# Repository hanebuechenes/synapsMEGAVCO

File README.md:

# synapsVCO 🎛️⚡

**synapsVCO** ist ein kompakter, leistungsstarker und professioneller Eurorack-Wavetable-VCO (Voltage Controlled Oscillator) auf Basis des **ATmega328P** Mikrocontrollers. Entwickelt für performative Live-Einsätze, kombiniert das Modul eine rauscharme analoge Signalverarbeitung mit mächtigen digitalen Klangformungsmöglichkeiten auf ultra-kompakten **6 TE** (30,48 mm).

## 🔬 Hauptmerkmale & Features

* **High-Performance Audio Path:**
  * Dual 12-Bit DAC (**MCP4922**) für hochauflösende Audiosignale.
  * Symmetrische Pufferung und Rekonstruktionsfilterung über Quad Op-Amp (**TL074**).

* **Killer Performance-Features:**
  * **Hard-Sync (`SYNC_IN`):** Triggert sofortigen Phasen-Reset an Interrupt-Pin `PD0` für aggressive Lead-Sounds und Sync-Sweeps.
  * **Morph-CV (`MORPH_CV`):** Gepufferter CV-Modulationseingang (über TL074 auf ADC `PC3`) zur dynamischen Modulation von Wavetables, Wave-Folding oder Pulsweite.
  * **Hardware Sub-Oszillator (`SUB_OUT`):** Dezidierter Auskopplungspfad (1 Oktave tiefer) über ATmega-Digitalpin `PD6` mit DC-Blocker für solides Bass-Fundament.

* **Audio- & Kontroll-Schnittstellen:**
  * **1V/Oct Pitch CV (`CV_IN`):** Impedanzgewandelter Eingangs-Pfad mit Zener-Diodenschutz.
  * **Gate In (`GATE_IN`) & Clock In (`CLOCK_IN`):** Dedizierte Digital-Eingänge für rhythmische Noten- und Takt-Trigger.
  * **Stereo/Dual Audio-Out (`AudioOut_L` / `AudioOut_R`).**

* **Robuste Stromversorgung & Protection:**
  * Bipolare $\pm 12\text{V}$ Eurorack-Versorgung.
  * Schutz vor Verpolung durch Schottky-Dioden (`MBRA140T3G`) und rückstellende Polyfuses (`250mA`).
  * Rauschfreie $\pm 12\text{VA}$ Analogschienen durch LC-Filterung (Ferrite Beads `120R@100MHz` + Entkopplungskondensatoren).
  * Effizienter Onboard 5V DC/DC-Schaltregler (`TPS54302`).

## 📏 Formfaktor & Layout

* **Breite:** 6 TE (30,48 mm)
* **Höhe:** Standard Eurorack 3U (128,5 mm Frontplatte / ~108,5 mm Platine)
* **Bauteil-Spezifikation:** Durchgängig **0603 SMD-Komponenten** (resistors/caps) für optimale Packungsdichte bei hervorragender manueller Lötbarkeit.

## 🛠️ Hardware-Architektur & Belegung

### Pin-Mapping (ATmega328P-AU TQFP-32)

| Pin | Symbol / Net | Funktion / Beschreibung |
| :--- | :--- | :--- |
| **Pin 30** | `PD0` | **Hard-Sync Input** (External Interrupt) |
| **Pin 32** | `PD2` | **Gate Input** |
| **Pin 1** | `PD3` | **Clock Input** |
| **Pin 10** | `PD6` | **Sub-Oszillator Output** |
| **Pin 25** | `PC2 / ADC2` | **1V/Oct CV Input** |
| **Pin 26** | `PC3 / ADC3` | **Morph-CV Input** |
| **Pin 23 / 24** | `PC0 / PC1` | **Potentiometer 1 & 2** (Parametertrimmer) |
| **Pin 14–17** | `PB2–PB5` | **SPI Interface** (MCP4922 DAC Steuerung) |
| **Pin 7 / 8** | `XTAL1 / XTAL2` | **16 MHz Quarz-Taktgeber** |

## 📋 Bauteilübersicht (BOM Kurzfassung)

* **Microcontroller:** ATmega328P-AU (TQFP-32)
* **DAC:** MCP4922-E/SL (SOIC-14)
* **Op-Amp:** TL074CDR (SOIC-14)
* **Power Regulator:** TPS54302 (SOT-23-6)
* **Dioden:** MBRA140T3G (SMA), B340A (SMA), 5.1V Zener (SOD-123)
* **Buchsen:** 3.5mm PJ301M-12 (THT)
* **Potentiometer:** Alpha RK09K Serie (THT)

## ⚡ Inbetriebnahme & Flashen

1. **Power-Check:** Vor dem Einsetzen von ICs oder der Firmware-Programmierung sicherstellen, dass an den Power-Rails des TL074 $+12\text{V}$ (Pin 4) und $-12\text{V}$ (Pin 11) anliegen sowie die Mikrocontroller-Schiene exakt $+5\text{V}$ aufweist.
2. **ISP-Programming:** Das Modul verfügt über einen Standard **2x3-Pin ISP Header** (`J2`).
3. **Fuses setzen:** Für den externen 16 MHz Quarz (`Y2`):
   * High Fuse: `0xD9`
   * Low Fuse: `0xFF`
   * Extended Fuse: `0xFD`

## 📄 Lizenz

Dieses Projekt ist Open-Source-Hardware unter der **CERN-OHL-P (Permissive)** Lizenz.

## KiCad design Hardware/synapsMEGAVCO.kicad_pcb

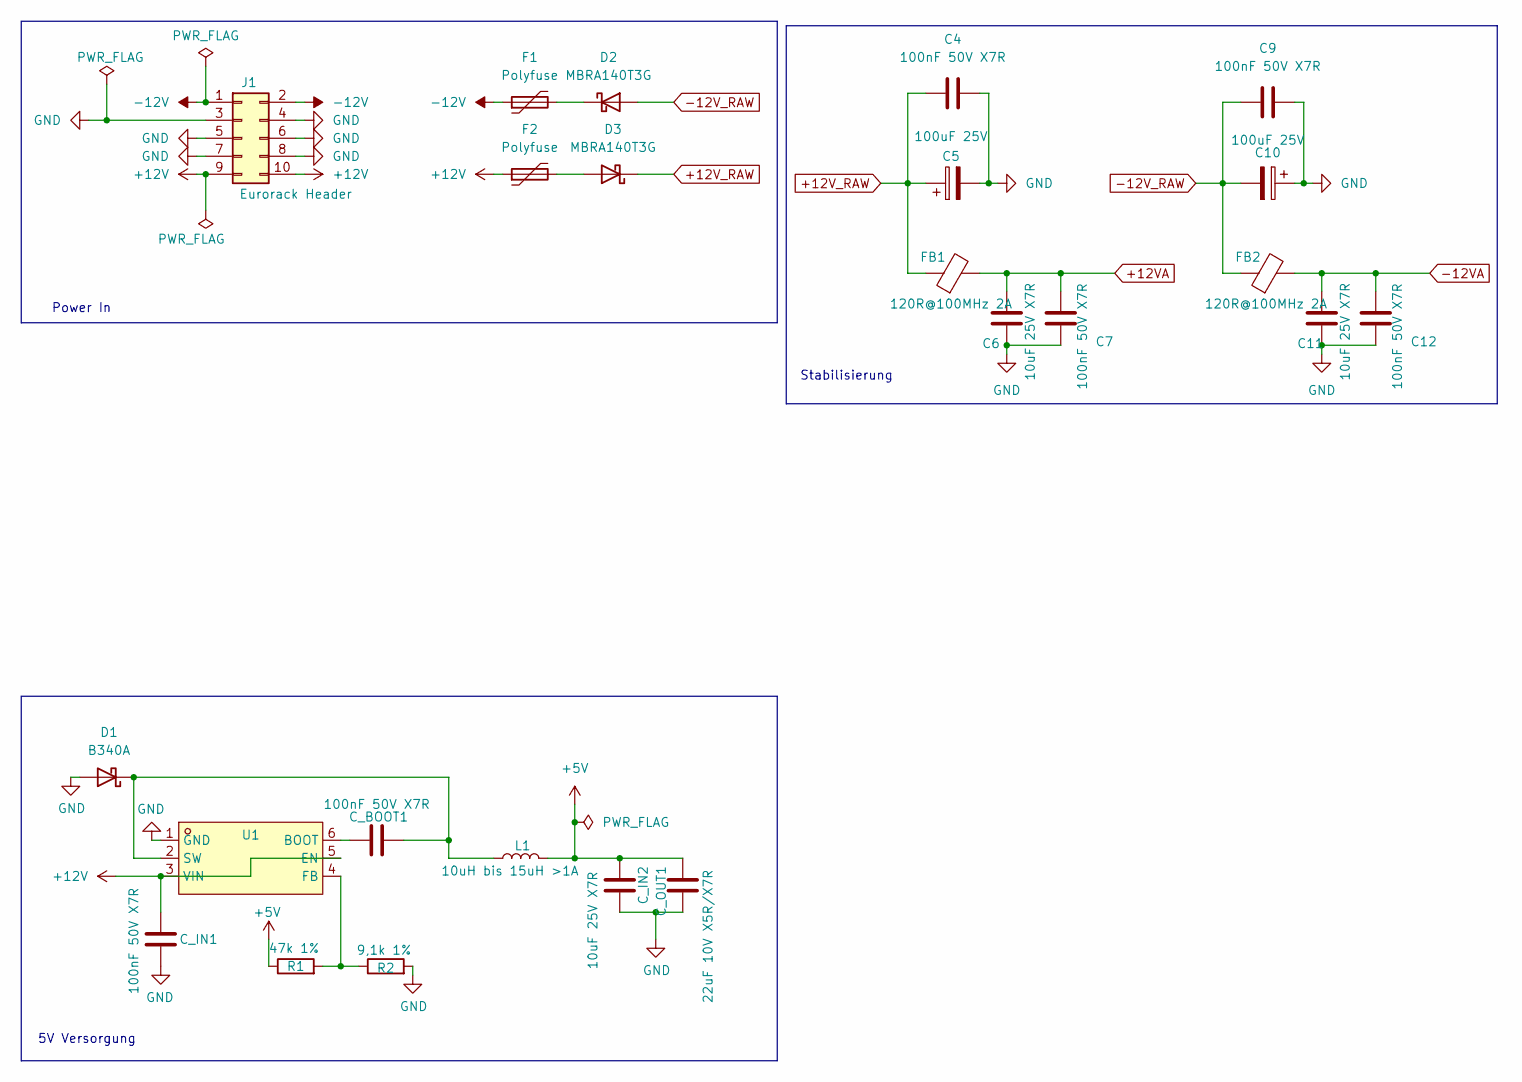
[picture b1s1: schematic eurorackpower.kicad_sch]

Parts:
C4, C7, C9, C12: 100nF 50V X7R; C_0603_1608Metric_Pad1.08x0.95mm_HandSolder
C5, C10: 100uF 25V; CP_Elec_6.3x7.7
C6, C11: 10uF 25V X7R; C_0805_2012Metric_Pad1.18x1.45mm_HandSolder
C_BOOT1: 100nF 50V X7R; C_0603_1608Metric_Pad1.08x0.95mm_HandSolder
C_IN1: 100nF 50V X7R; C_0603_1608Metric_Pad1.08x0.95mm_HandSolder
C_IN2: 10uF 25V X7R; C_0805_2012Metric_Pad1.18x1.45mm_HandSolder
C_OUT1: 22uF 10V X5R/X7R; C_0805_2012Metric_Pad1.18x1.45mm_HandSolder
D1: B340A; D_SMA
D2, D3: MBRA140T3G; D_SMA
F1, F2: Polyfuse; Fuse_1210_3225Metric
FB1, FB2: 120R@100MHz 2A; L_0603_1608Metric_Pad1.05x0.95mm_HandSolder
J1: Eurorack Header; PinHeader_2x05_P2.54mm_Vertical
L1: 10uH bis 15uH >1A; L_Coilcraft_XxL4030
R1: 47k 1%; R_0603_1608Metric_Pad0.98x0.95mm_HandSolder
R2: 9,1k 1%; R_0603_1608Metric_Pad0.98x0.95mm_HandSolder
U1: TPS54302DDCR_C311983; SOT-23-6_L2.9-W1.6-P0.95-LS2.8-BL; MPN TPS54302DDCR; LCSC Part C311983

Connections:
+5V: C_IN2.1, C_OUT1.1, L1.2, R1.1; also elsewhere on the board
+12V: C_IN1.1, F2.1, J1.9, J1.10, U1.3 (VIN), U1.5 (EN)
+12VA: C6.1, C7.1, FB1.2; also elsewhere on the board
+12V_RAW: C4.1, C5.1, D3.1 (K), FB1.1
-12V: F1.1, J1.1, J1.2
-12VA: C11.1, C12.1, FB2.2; also elsewhere on the board
-12V_RAW: C9.1, C10.2, D2.2 (A), FB2.1
GND: C4.2, C5.2, C6.2, C7.2, C9.2, C10.1, C11.2, C12.2, C_IN1.2, C_IN2.2, C_OUT1.2, D1.2 (A), J1.3, J1.4, J1.5, J1.6, J1.7, J1.8, R2.2, U1.1 (GND); also elsewhere on the board
unnamed: C_BOOT1.2, D1.1 (K), L1.1, U1.2 (SW)
unnamed: D2.1 (K), F1.2
unnamed: D3.2 (A), F2.2
unnamed: C_BOOT1.1, U1.6 (BOOT)
unnamed: R1.2, R2.1, U1.4 (FB)

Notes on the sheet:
5V Versorgung
Power In
Stabilisierung

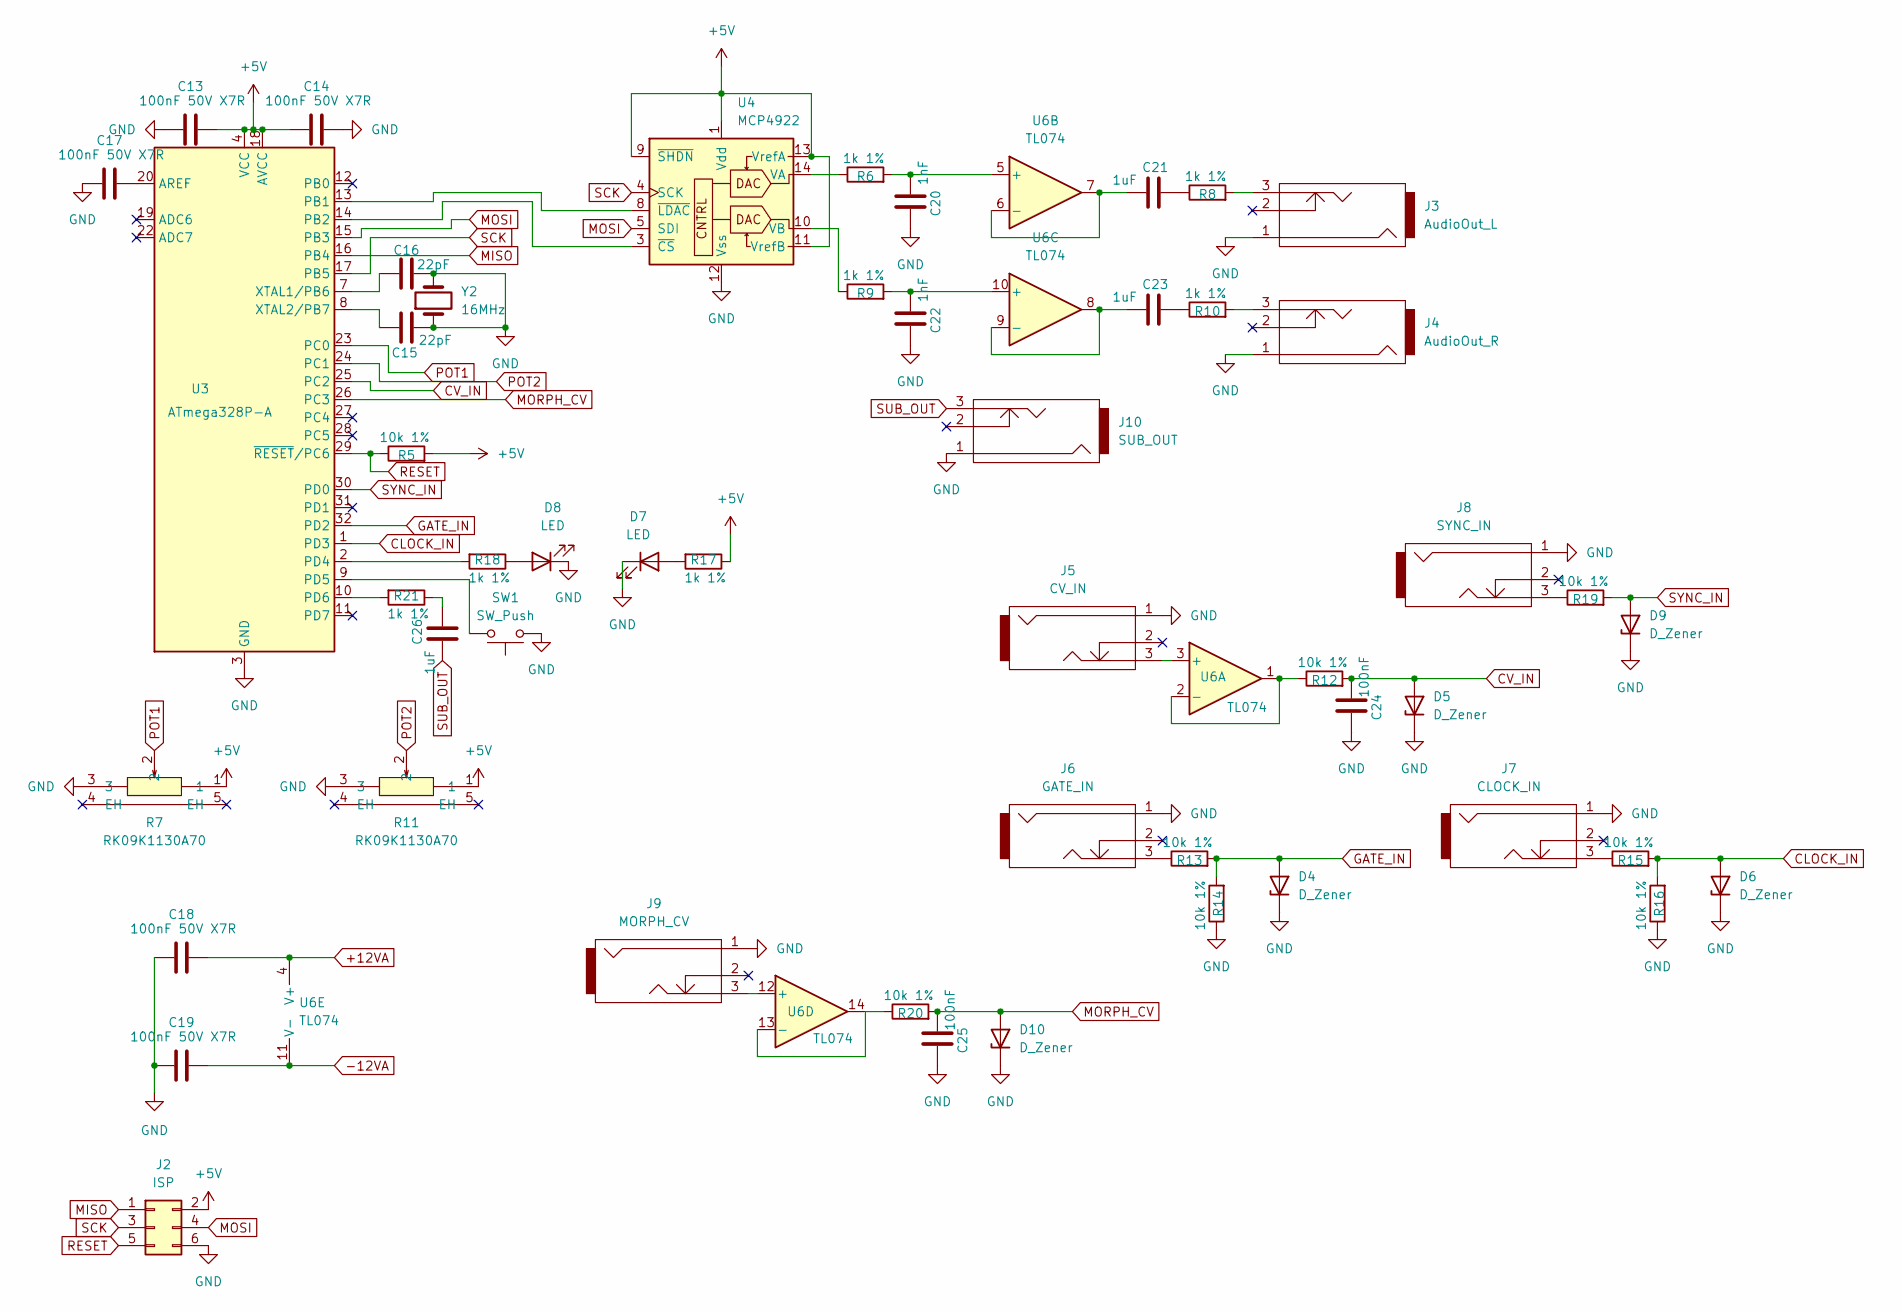
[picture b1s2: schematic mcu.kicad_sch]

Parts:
C13, C14, C17, C18, C19: 100nF 50V X7R; C_0603_1608Metric_Pad1.08x0.95mm_HandSolder
C15, C16: 22pF; C_0603_1608Metric_Pad1.08x0.95mm_HandSolder
C20, C22: 1nF; C_0603_1608Metric_Pad1.08x0.95mm_HandSolder
C21, C23, C26: 1uF; C_0603_1608Metric_Pad1.08x0.95mm_HandSolder
C24, C25: 100nF; C_0603_1608Metric_Pad1.08x0.95mm_HandSolder
D4, D5, D6, D9, D10: D_Zener; D_SOD-123
D7, D8: LED; led-3mm
J2: ISP; PinHeader_2x03_P2.54mm_Vertical
J3: AudioOut_L; PJ301M-12; MFG Part Number WQP-WQP518MA; Digikey Part Number N/A
J4: AudioOut_R; PJ301M-12; MFG Part Number WQP-WQP518MA; Digikey Part Number N/A
J5: CV_IN; PJ301M-12; MFG Part Number WQP-WQP518MA; Digikey Part Number N/A
J6: GATE_IN; PJ301M-12; MFG Part Number WQP-WQP518MA; Digikey Part Number N/A
J7: CLOCK_IN; PJ301M-12; MFG Part Number WQP-WQP518MA; Digikey Part Number N/A
J8: SYNC_IN; PJ301M-12; MFG Part Number WQP-WQP518MA; Digikey Part Number N/A
J9: MORPH_CV; PJ301M-12; MFG Part Number WQP-WQP518MA; Digikey Part Number N/A
J10: SUB_OUT; PJ301M-12; MFG Part Number WQP-WQP518MA; Digikey Part Number N/A
R5, R12, R13, R14, R15, R16, R19, R20: 10k 1%; R_0603_1608Metric_Pad0.98x0.95mm_HandSolder
R6, R8, R9, R10, R17, R18, R21: 1k 1%; R_0603_1608Metric_Pad0.98x0.95mm_HandSolder
R7, R11: RK09K1130A70; RES-TH_RK09K1130A70; MPN RK09K1130A70; LCSC Part C351173
SW1: SW_Push; SW_PUSH_6mm
U3: ATmega328P-A; TQFP-32_7x7mm_P0.8mm
U4: MCP4922; SOIC-14_3.9x8.7mm_P1.27mm
U6: TL074; SOIC-14_L8.7-W3.9-P1.27-LS6.0-BL
Y2: 16MHz; Crystal_HC49-U_Vertical

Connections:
+5V: C13.2, C14.1, J2.2, R5.2, R7.1, R11.1, R17.1, U3.4 (VCC), U3.6 (VCC), U3.18 (AVCC), U4.1 (Vdd), U4.9 (~SHDN), U4.11 (VrefB), U4.13 (VrefA); also elsewhere on the board
+12VA: C18.2, U6.4 (V+); also elsewhere on the board
-12VA: C19.2, U6.11 (V-); also elsewhere on the board
CLOCK_IN: D6.2 (A), R15.2, R16.2, U3.1 (PD3)
CV_IN: C24.2, D5.2 (A), R12.2, U3.25 (PC2)
GATE_IN: D4.2 (A), R13.2, R14.2, U3.32 (PD2)
GND: C13.1, C14.2, C15.2, C16.2, C17.1, C18.1, C19.1, C20.1, C22.1, C24.1, C25.1, D4.1 (K), D5.1 (K), D6.1 (K), D7.1 (K), D8.1 (K), D9.1 (K), D10.1 (K), J2.6, J3.1, J4.1, J5.1, J6.1, J7.1, J8.1, J9.1, J10.1, R7.3, R11.3, R14.1, R16.1, SW1.1, U3.3 (GND), U3.5 (GND), U3.21 (GND), U4.12 (Vss), Y2.1, Y2.2; also elsewhere on the board
MISO: J2.1, U3.16 (PB4)
MORPH_CV: C25.2, D10.2 (A), R20.2, U3.26 (PC3)
MOSI: J2.4, U3.15 (PB3), U4.5 (SDI)
unnamed: C21.1, R8.1
unnamed: C23.1, R10.1
unnamed: C26.1, R21.1
unnamed: D7.2 (A), R17.2
unnamed: D8.2 (A), R18.1
unnamed: J3.3, R8.2
unnamed: J4.3, R10.2
unnamed: J6.3, R13.1
unnamed: J7.3, R15.1
unnamed: J8.3, R19.1
unnamed: C17.2, U3.20 (AREF)
unnamed: U3.13 (PB1), U4.8 (~LDAC)
unnamed: U3.14 (PB2), U4.3 (~CS)
unnamed: R18.2, U3.2 (PD4)
unnamed: SW1.2, U3.9 (PD5)
unnamed: R21.2, U3.10 (PD6)
unnamed: C16.1, U3.7 (XTAL1/PB6)
unnamed: C15.1, U3.8 (XTAL2/PB7)
unnamed: R6.1, U4.14 (VA)
unnamed: R9.1, U4.10 (VB)
unnamed: J5.3, U6.3 (+)
unnamed: R12.1, U6.1, U6.2 (-)
unnamed: C20.2, R6.2, U6.5 (+)
unnamed: C21.2, U6.6 (-), U6.7
unnamed: C22.2, R9.2, U6.10 (+)
unnamed: C23.2, U6.8, U6.9 (-)
unnamed: J9.3, U6.12 (+)
unnamed: R20.1, U6.13 (-), U6.14
POT1: R7.2, U3.23 (PC0)
POT2: R11.2, U3.24 (PC1)
RESET: J2.5, R5.1, U3.29 (~RESET/PC6)
SCK: J2.3, U3.17 (PB5), U4.4 (SCK)
SUB_OUT: C26.2, J10.3
SYNC_IN: D9.2 (A), R19.2, U3.30 (PD0)

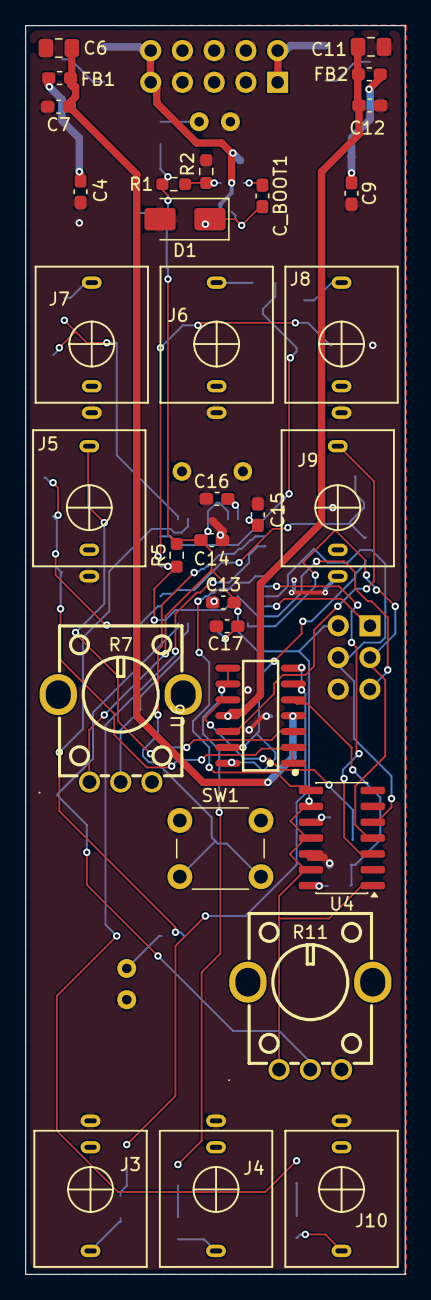
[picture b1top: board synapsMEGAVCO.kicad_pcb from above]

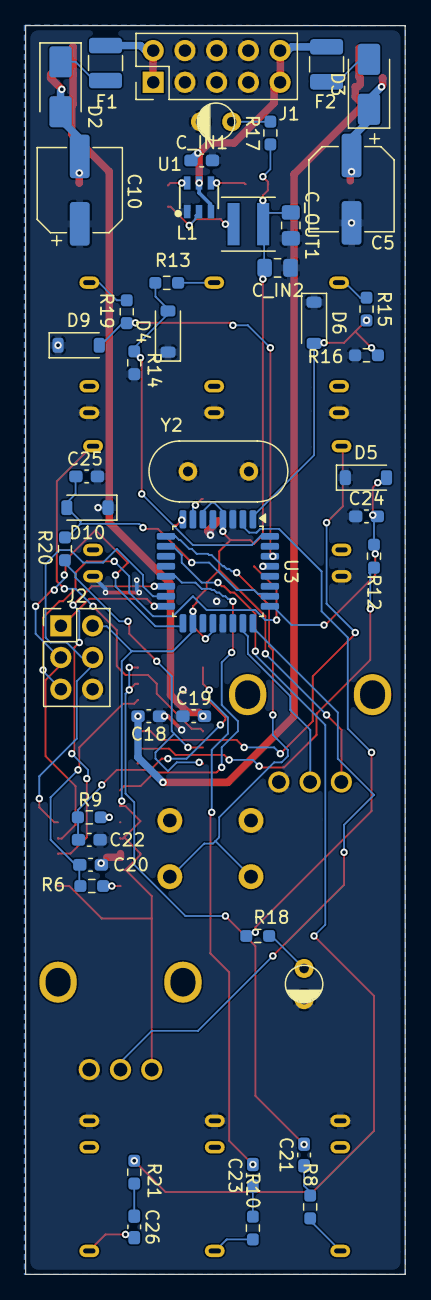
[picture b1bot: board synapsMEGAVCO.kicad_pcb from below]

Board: 2 copper layers, 30.4 x 100.0 mm, 76 parts (45 on the bottom side), 53 nets.

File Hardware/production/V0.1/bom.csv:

Designator,Footprint,Quantity,Value,LCSC Part #
"C10, C5",CP_Elec_6.3x7.7,2,100uF 25V,
"C11, C6, C_IN2",0805,3,10uF 25V X7R,
"C12, C13, C14, C17, C18, C19, C4, C7, C9, C_BOOT1, C_IN1",0603,11,100nF 50V X7R,
"C15, C16",0603,2,22pF,
"C20, C22",0603,2,1nF,
"C21, C23, C26",0603,3,1uF,
"C24, C25",0603,2,100nF,
C_OUT1,0805,1,22uF 10V X5R/X7R,
D1,D_SMA,1,B340A,
"D10, D4, D5, D6, D9",D_SOD-123,5,D_Zener,
"D2, D3",D_SMA,2,MBRA140T3G,
"D7, D8",led-3mm,2,LED,
"F1, F2",1210,2,Polyfuse,
"FB1, FB2",0603,2,120R@100MHz 2A,
J1,PinHeader_2x05_P2.54mm_Vertical,1,Eurorack Header,
J10,PJ301M-12,1,SUB_OUT,
J2,PinHeader_2x03_P2.54mm_Vertical,1,ISP,
J3,PJ301M-12,1,AudioOut_L,
J4,PJ301M-12,1,AudioOut_R,
J5,PJ301M-12,1,CV_IN,
J6,PJ301M-12,1,GATE_IN,
J7,PJ301M-12,1,CLOCK_IN,
J8,PJ301M-12,1,SYNC_IN,
J9,PJ301M-12,1,MORPH_CV,
L1,L_Coilcraft_XxL4030,1,10uH bis 15uH >1A,
R1,0603,1,47k 1%,
"R10, R17, R18, R21, R6, R8, R9",0603,7,1k 1%,
"R11, R7",RES-TH_RK09K1130A70,2,RK09K1130A70,C351173
"R12, R13, R14, R15, R16, R19, R20, R5",0603,8,10k 1%,
R2,0603,1,"9,1k 1%",
SW1,SW_PUSH_6mm,1,SW_Push,
U1,SOT-23-6_L2.9-W1.6-P0.95-LS2.8-BL,1,TPS54302DDCR_C311983,C311983
U3,TQFP-32_7x7mm_P0.8mm,1,ATmega328P-A,
U4,SOIC-14_3.9x8.7mm_P1.27mm,1,MCP4922,
U6,SOIC-14_L8.7-W3.9-P1.27-LS6.0-BL,1,TL074,
Y2,Crystal_HC49-U_Vertical,1,16MHz,
